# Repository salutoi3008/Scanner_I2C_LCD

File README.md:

# Scanner I2C LCD

Mini-projet de conception PCB – BTS CIEL 2 (Électronique et Réseaux)

Scanner d'adresses I2C autonome, basé sur un microcontrôleur **ATtiny84** et un écran LCD **HD44780**. Il suffit de brancher un composant I2C sur le scanner : la première adresse détectée s'affiche sur l'écran, sans avoir besoin d'un ordinateur ni de la documentation du composant.

## Objectif

Proposer un circuit imprimé prêt à être fabriqué :

- une seule face de pistes (et éventuellement quelques ponts)
- format Eurocard sans connecteur de rack
- sérigraphie complète (nom du concepteur, du fichier, date)
- routage à la main, en brouillant les pistes (approche « cyber »)
- composants brasés sur le PCB, selon la nomenclature imposée
- points de test placés judicieusement

## Nomenclature de base

| Désignation | Valeur | Quantité |
|---|---|---|
| Microcontrôleur | ATtiny84 P-PU | 1 |
| Écran LCD | Hitachi HD44780 | 1 |
| Bornes de connexion | PinHeader | [à définir] |
| Bornier à vis | 5,08 mm | 1 |
| Résistances | 4,7 kΩ | 2 |
| Potentiomètre | 10 kΩ horizontal | 1 |

## Organisation du dépôt

```
Scanner_I2C_LCD/
├── README.md
├── docs/                 Sujet du projet et datasheets
├── kicad/                Projet KiCad (schéma + PCB)
├── simulation/           Projet SimulIDE et captures
├── code/                 Code C (IDE Arduino)
└── dossier_technique/    Nomenclature, SysML, gamme de montage, tests
```

## Outils utilisés

- **KiCad** : schéma et routage du PCB
- **SimulIDE** : simulation préalable
- **Arduino IDE** : programmation de l'ATtiny84 en C

## Auteur

Enzo – BTS CIEL 2, Lycée Paul Langevin – 2026-2027

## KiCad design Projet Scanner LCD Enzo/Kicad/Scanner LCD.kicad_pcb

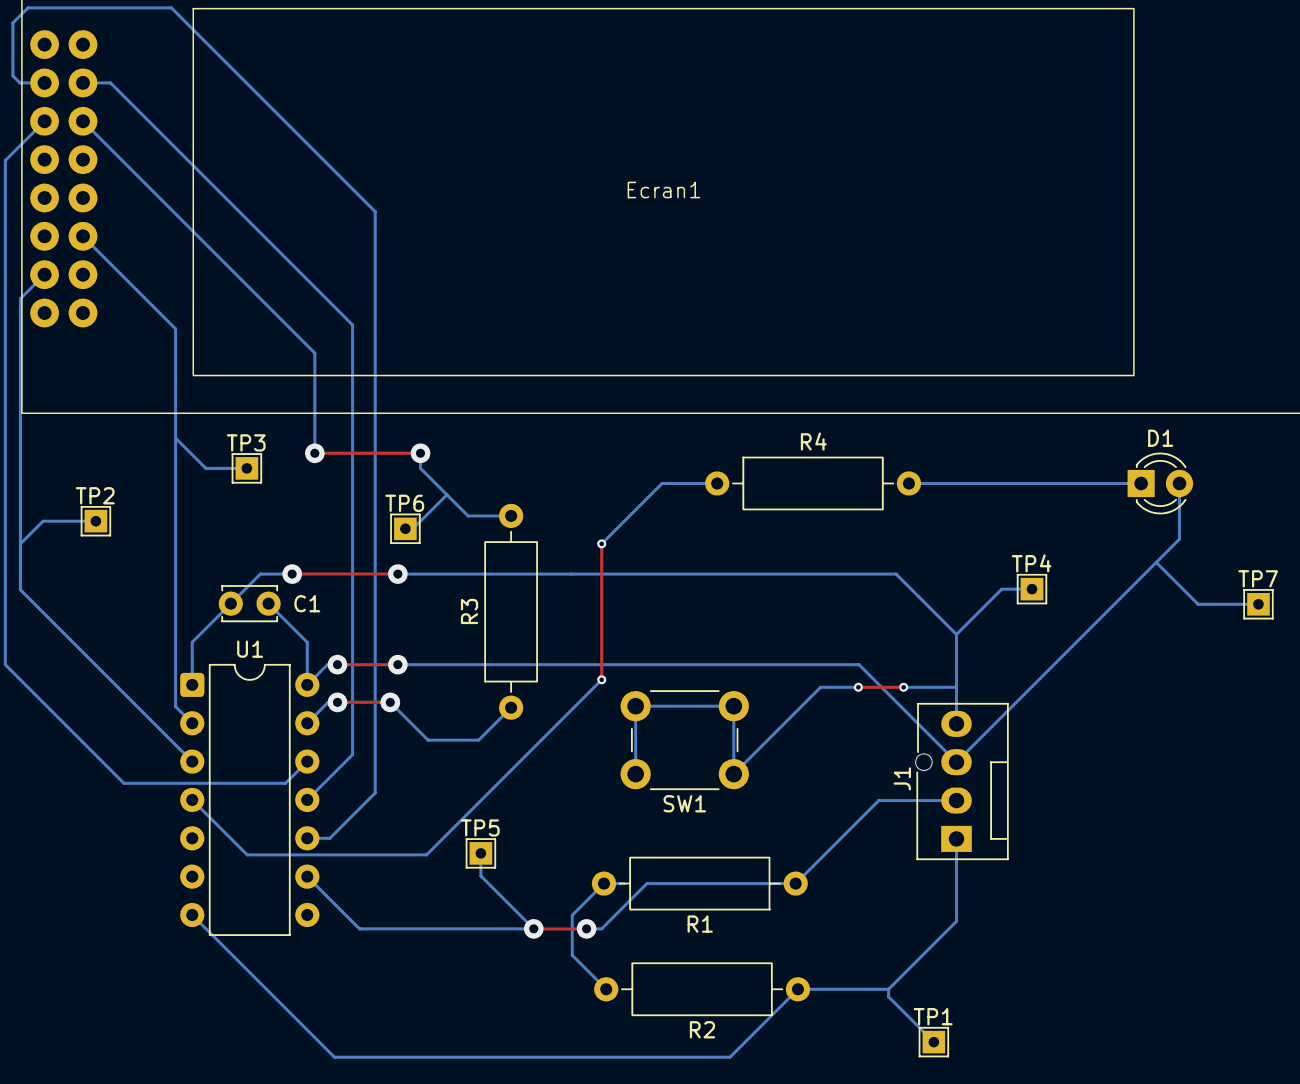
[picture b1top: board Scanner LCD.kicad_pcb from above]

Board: 2 copper layers, 17 parts (0 on the bottom side), 14 nets.

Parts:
C1: 100nF; C_Disc_D3.4mm_W2.1mm_P2.50mm
D1: LED; LED_D3.0mm
Ecran1: Sans titre
J1: Conn_01x04_Pin; FanPinHeader_1x04_P2.54mm_Vertical
R1, R2: 4700; R_Axial_DIN0309_L9.0mm_D3.2mm_P12.70mm_Horizontal
R3: 0; R_Axial_DIN0309_L9.0mm_D3.2mm_P12.70mm_Horizontal
R4: 150; R_Axial_DIN0309_L9.0mm_D3.2mm_P12.70mm_Horizontal
SW1: SW_MEC_5G; SW_PUSH_6mm_H5mm
TP1, TP2, TP3, TP4, TP5, TP6, TP7: TestPoint; TestPoint_THTPad_1.5x1.5mm_Drill0.7mm
U1: ATtiny44A-P; DIP-14_W7.62mm

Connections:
+5V: C1.2, J1.4, SW1.1 (A), SW1.2 (A), TP4.1, U1.1 (VCC)
GND: C1.1, D1.2 (A), J1.3, TP7.1, U1.14 (GND)
unnamed: D1.1 (K), R4.2
unnamed: Ecran1.11 (DB4), R3.2, TP6.1
unnamed: Ecran1.12 (DB5), U1.12 (PA1)
unnamed: Ecran1.13 (DB6), U1.11 (PA2)
unnamed: Ecran1.14 (DB7), U1.10 (PA3)
unnamed: Ecran1.6 (E), TP3.1, U1.2 (XTAL1/PB0)
unnamed: Ecran1.4 (RS), TP2.1, U1.3 (XTAL2/PB1)
unnamed: J1.1, R2.1, TP1.1, U1.7 (PA6)
unnamed: J1.2, R1.1, TP5.1, U1.9 (PA4)
unnamed: R1.2, R2.2
unnamed: R3.1, U1.13 (AREF/PA0)
unnamed: R4.1, U1.4 (~RESET/PB3)
